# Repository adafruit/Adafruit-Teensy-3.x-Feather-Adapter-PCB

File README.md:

## Adafruit Teensy 3.x Feather Adapter PCB
<a href="http://www.adafruit.com/products/3200"><br/>
Click here to purchase one from the Adafruit shop</a>

This Feather adapter rearranges the pins of a Teensy 3.x to give you the same shape and pinout for our Feathers. We've tested our FeatherWings so far and all are drop-in compatible. It's a great way to take advantage of the Feather ecosystem. Give your Teensy a stepper/DC motor driver, GPS, LED matrix or OLED add-on with ease. With the space left over, we even added in a 500mA LiPoly charger that automatically charges over USB and will switch over to the LiPo when USB is unplugged. There's also a 100K resistor divider for monitoring the battery voltage connected to A7

PCB files for the Adafruit Teensy 3.x Feather Adapter. The format is EagleCAD schematic and board layout
- https://www.adafruit.com/product/3200

### License

Adafruit invests time and resources providing this open source design, please support Adafruit and open-source hardware by purchasing products from [Adafruit](https://www.adafruit.com)!

All text above must be included in any redistribution

Designed by Limor Fried/Ladyada for Adafruit Industries.
Creative Commons Attribution/Share-Alike, all text above must be included in any redistribution. 
See license.txt for additional information.

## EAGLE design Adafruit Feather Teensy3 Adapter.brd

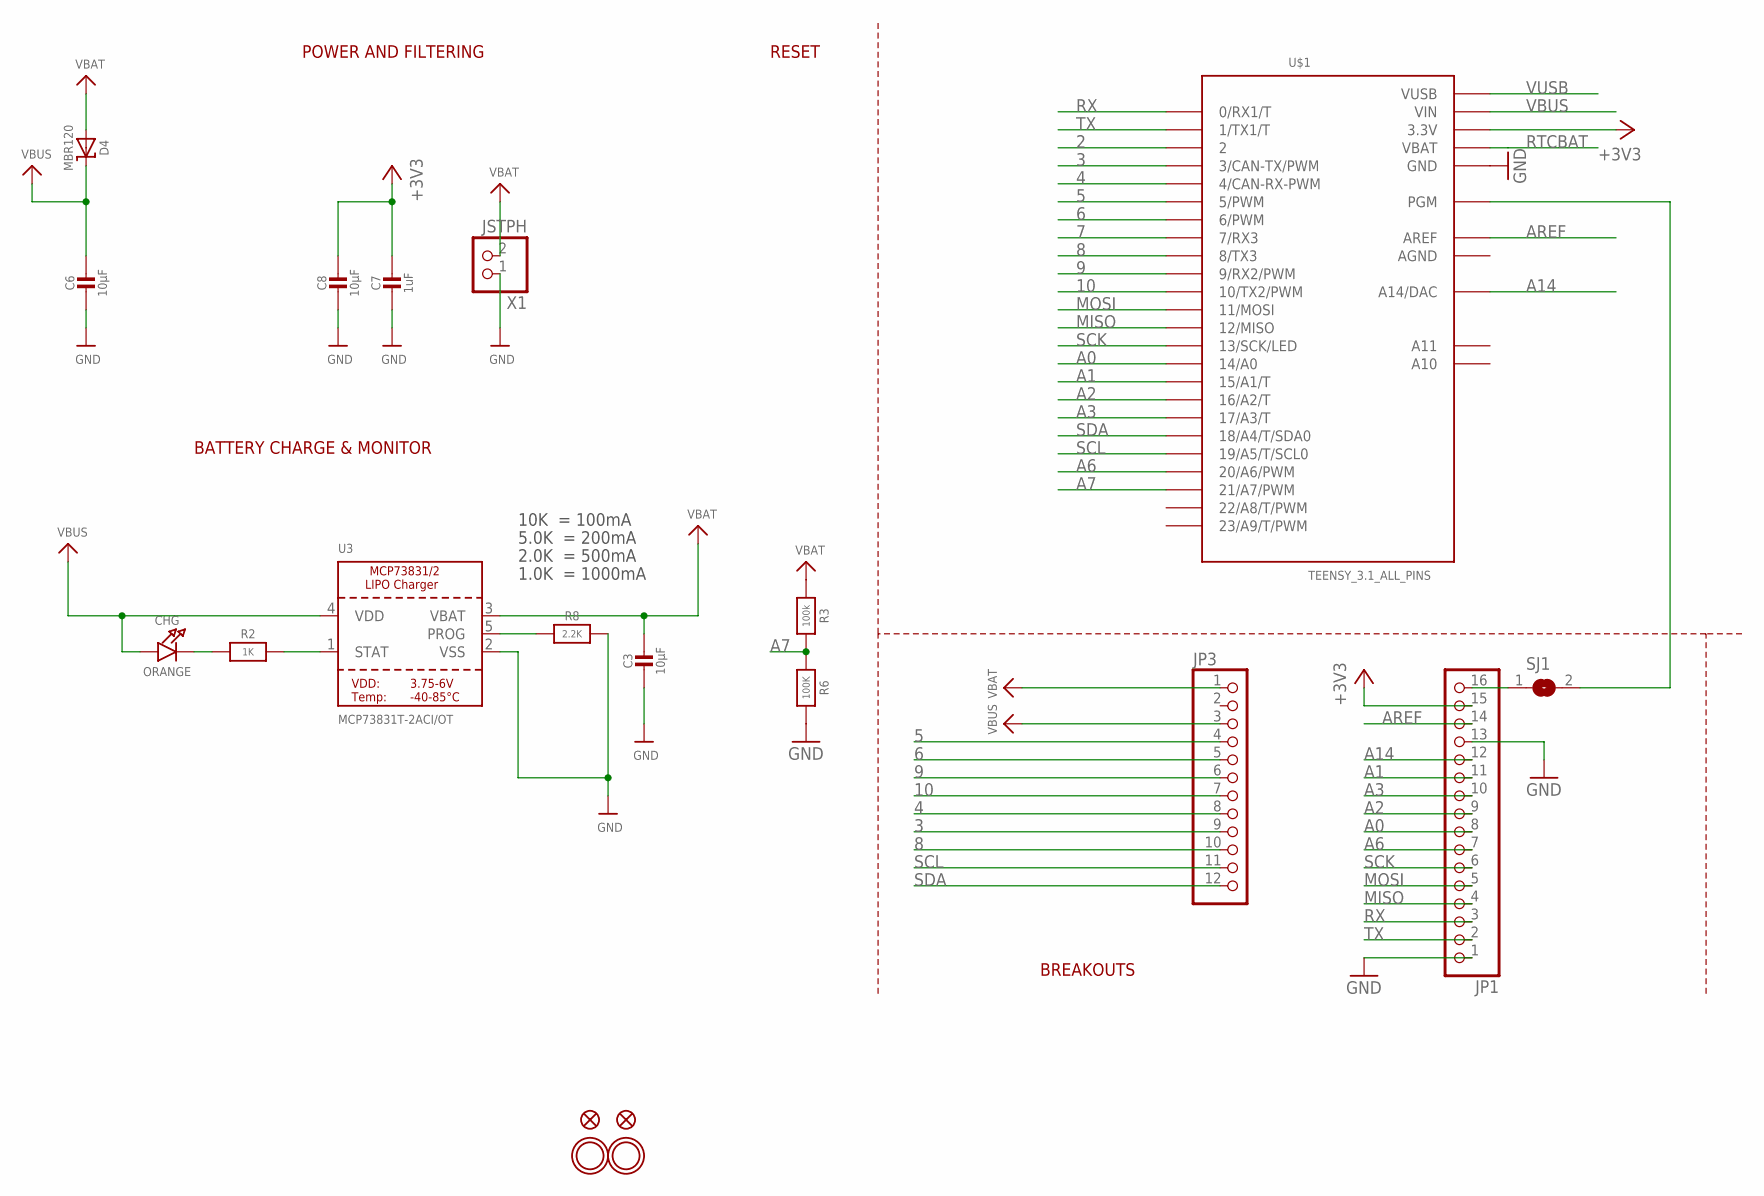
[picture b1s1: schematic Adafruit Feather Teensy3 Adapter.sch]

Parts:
C3, C6, C8: 10µF; 0805-NO
C7: 1uF; 0603-NO
CHG: ORANGE; CHIPLED_0805_NOOUTLINE
D4: MBR120; SOD-123
JP1: HEADER-1X16ROUND; 1X16_ROUND
JP3: HEADER-1X12; 1X12_ROUND
R2: 1K; 0603-NO
R3: 100k; 0603-NO
R6: 100K; 0603-NO
R8: 2.2K; 0603-NO
SJ1: SOLDERJUMPERCLOSED; SOLDERJUMPER_CLOSEDWIRE
U3: MCP73831T-2ACI/OT; SOT23-5
U$1: TEENSY_3.1_ALL_PINS; TEENSY3-ALL_PINS
U$31, U$32: MOUNTINGHOLE2.5; MOUNTINGHOLE_2.5_PLATED
U$34, U$35: FIDUCIAL""; FIDUCIAL_1MM
X1: JSTPH; JSTPH2

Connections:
2: U$1.2
3: JP3.9, U$1.3 (3/CAN-TX/PWM)
4: JP3.8, U$1.4 (4/CAN-RX-PWM)
5: JP3.4, U$1.5 (5/PWM)
6: JP3.5, U$1.6 (6/PWM)
7: U$1.7 (7/RX3)
8: JP3.10, U$1.8 (8/TX3)
9: JP3.6, U$1.9 (9/RX2/PWM)
10: JP3.7, U$1.10 (10/TX2/PWM)
+3V3: C7.1, C8.1, JP1.15, U$1.3.3V, U$1.3.3V1 (3.3V)
A0: JP1.8, U$1.14/A0
A1: JP1.11, U$1.15/A1 (15/A1/T)
A2: JP1.9, U$1.16/A2 (16/A2/T)
A3: JP1.10, U$1.17/A3 (17/A3/T)
A6: JP1.7, U$1.20/A6 (20/A6/PWM)
A7: R3.2, R6.1, U$1.21/A7 (21/A7/PWM)
A14: JP1.12, U$1.RESET/DAC (A14/DAC)
AGND: U$1.AGND
AREF: JP1.14, U$1.AREF
BOOT: SJ1.2, U$1.PGM
GND: C3.2, C6.2, C7.2, C8.2, JP1.1, JP1.13, R6.2, R8.2, U3.2 (VSS), U$1.GND, U$1.GND1 (GND), X1.1
MISO: JP1.4, U$1.12 (12/MISO)
MOSI: JP1.5, U$1.11 (11/MOSI)
unnamed: CHG.C, R2.1
unnamed: R2.2, U3.1 (STAT)
unnamed: R8.1, U3.5 (PROG)
RST/BOOT: JP1.16, SJ1.1
RTCBAT: U$1.VBAT
RX: JP1.3, U$1.0 (0/RX1/T)
SCK: JP1.6, U$1.13 (13/SCK/LED)
SCL: JP3.11, U$1.19/A5 (19/A5/T/SCL0)
SDA: JP3.12, U$1.18/A4 (18/A4/T/SDA0)
TX: JP1.2, U$1.1 (1/TX1/T)
VBAT: C3.1, D4.A, JP3.1, R3.1, U3.3 (VBAT), X1.2
VBUS: C6.1, CHG.A, D4.C, JP3.3, U3.4 (VDD), U$1.VIN
VUSB: U$1.VUSB

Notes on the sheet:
POWER AND FILTERING
RESET
10K = 100mA
5.0K = 200mA
2.0K = 500mA
1.0K = 1000mA
BATTERY CHARGE & MONITOR
BREAKOUTS

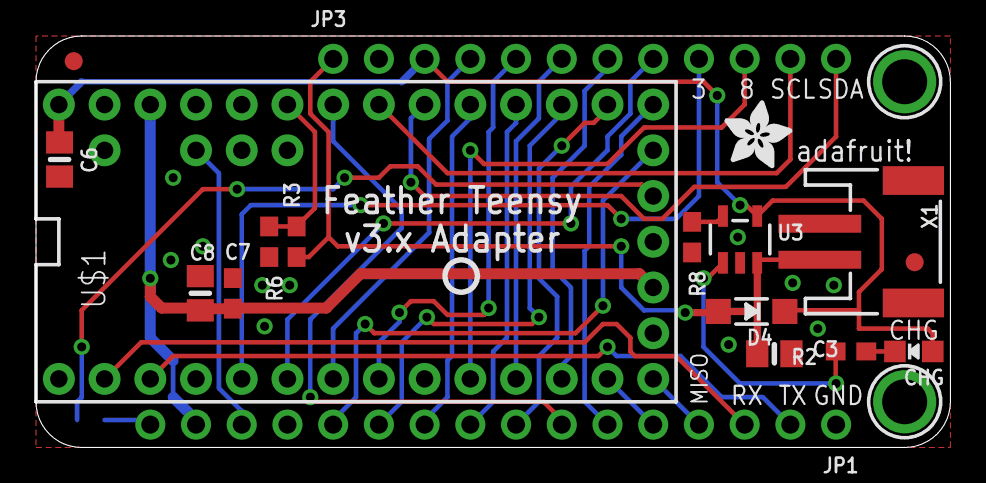
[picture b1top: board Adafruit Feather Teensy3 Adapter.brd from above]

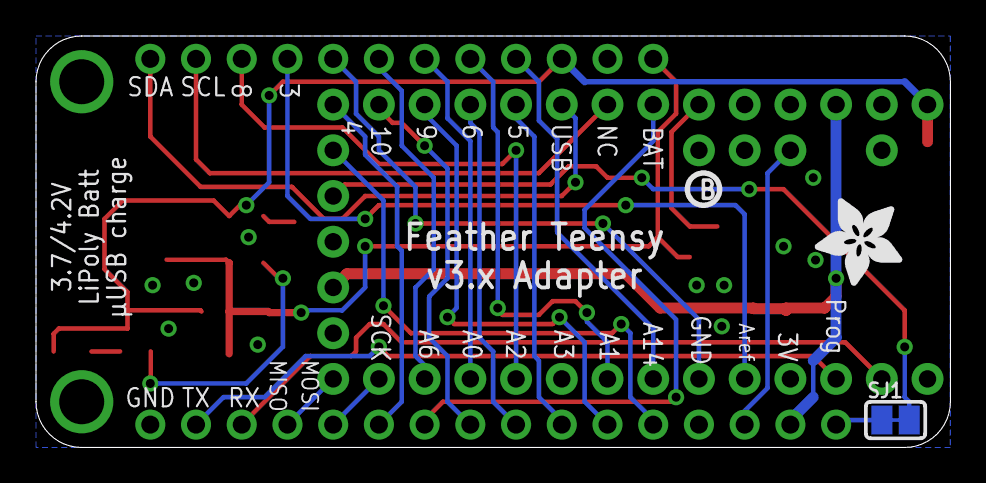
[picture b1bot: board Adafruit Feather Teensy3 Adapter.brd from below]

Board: 2 copper layers, 50.8 x 22.9 mm, 24 parts (3 on the bottom side), 31 nets.

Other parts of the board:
U$4: ADAFRUIT_5MM
U$5, U$6: PCBFEAT-REV-040
U$7: ADAFRUIT_3.5MM

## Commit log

2016-08-03 init
2016-08-03 add schem
2020-09-03 Rename file.
2020-09-03 Adding latest board files.

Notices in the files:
parts and their libraries:
microbuilder: This work is placed in the public domain, and may be freely used for commercial and non-commercial work with the following conditions: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
